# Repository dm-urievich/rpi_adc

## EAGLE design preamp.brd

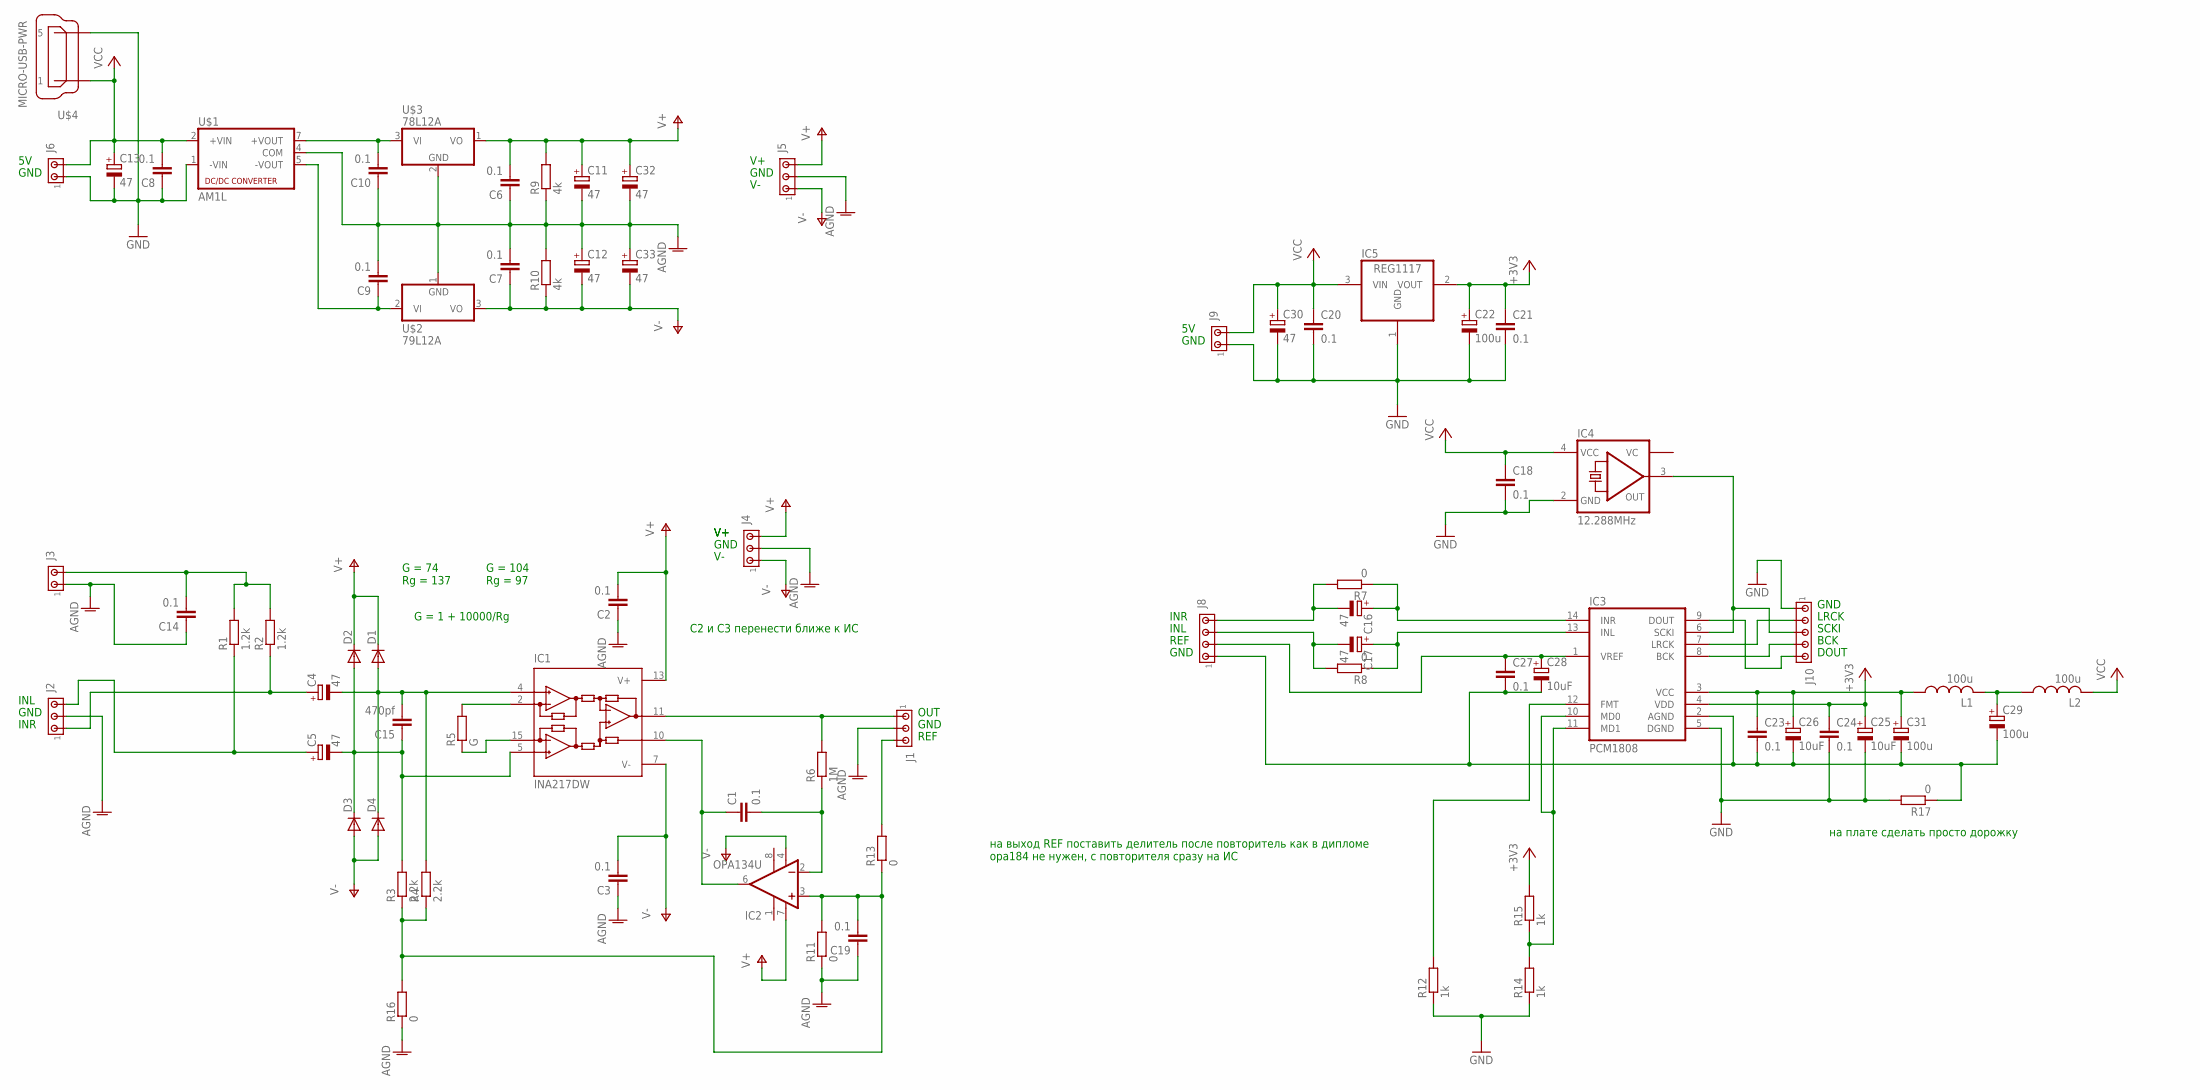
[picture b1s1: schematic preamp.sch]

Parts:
C1, C2, C3, C6, C7, C8, C9, C10, C14, C18, C19, C20, C21, C23, C24, C27: 0.1; C0805
C4, C5, C11, C12, C13, C16, C17, C30, C32, C33: 47; 153CLV-0605
C15: 470pf; C0805
C22, C29, C31: 100u; 153CLV-0605
C25, C26, C28: 10uF; SMC_A
D1, D2, D3, D4: DIODE-SOD123; SOD123
IC1: INA217DW; DW_RPDSO-G16
IC2: OPA134U; SO08
IC3: PCM1808; TSSOP14
IC4: 12.288MHz; KXO-97
IC5: REG1117; SOT223
J1, J2, J4, J5: MTA03-100; 10X03MTA
J3, J6, J9: MTA02-100; 10X02MTA
J8: MTA04-100; 10X04MTA
J10: MTA05-100; 10X05MTA
L1, L2: 100u; L3225M
R1, R2: 1.2k; R0805
R3, R4: 2.2k; R0805
R5: G; R0805
R6: 1M; R0805
R7, R8, R11, R13, R16, R17: 0; R0805
R9, R10: 4k; R0805
R12, R14, R15: 1k; R0805
U$1: AM1L; SO20
U$2: 79L12A; SOT89
U$3: 78L12A; SOT89
U$4: MICRO-USB-PWR; MICRO-USB

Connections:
+3V3: C21.1, C22.+, C24.1, C25.+, IC3.4 (VDD), IC5.2 (VOUT), R15.2
AGND: C2.1, C3.1, C6.1, C7.2, C9.2, C10.1, C11.-, C12.+, C14.1, C19.1, C32.-, C33.+, J1.2, J2.2, J3.1, J4.2, J5.2, R9.1, R10.2, R11.1, R16.1, U$1.4 (COM), U$2.1 (GND), U$3.2 (GND)
AGND2: C23.2, C26.-, C27.2, C28.-, C29.-, C31.-, IC3.2 (AGND), J8.1, R17.1
GND: C8.1, C13.-, C18.2, C20.2, C21.2, C22.-, C24.2, C25.-, C30.-, IC3.5 (DGND), IC4.2 (GND), IC5.1 (GND), J6.1, J9.1, J10.1, R12.1, R14.1, R17.2, U$1.1 (-VIN), U$4.5
unnamed: IC1.2 (RG1), R5.2
unnamed: IC1.15 (RG2), R5.1
unnamed: C5.-, C15.1, D2.A, D3.C, IC1.5 (+IN), R3.2
unnamed: C4.-, C15.2, D1.A, D4.C, IC1.4 (-IN), R4.2
unnamed: C4.+, J2.1, R2.1
unnamed: C5.+, J2.3, R1.1
unnamed: C10.2, U$1.7 (+VOUT), U$3.3 (VI)
unnamed: IC3.6 (SCKI), IC4.3 (OUT), J10.3
unnamed: IC3.9 (DOUT), J10.5
unnamed: C29.+, L1.2, L2.1
unnamed: C14.2, J3.2, R1.2, R2.2
unnamed: C1.2, IC2.2 (-IN), R6.1
unnamed: IC1.11 (OUT), J1.1, R6.2
unnamed: C1.1, IC1.10 (REF), IC2.6 (OUT)
unnamed: C9.1, U$1.5 (-VOUT), U$2.2 (VI)
unnamed: IC3.12 (FMT), R12.2
unnamed: IC3.7 (LRCK), J10.2
unnamed: IC3.8 (BCK), J10.4
unnamed: C27.1, C28.+, IC3.1 (VREF), J8.2
unnamed: C16.-, J8.4, R7.2
unnamed: C17.-, J8.3, R8.2
unnamed: C17.+, IC3.13 (INL), R8.1
unnamed: C16.+, IC3.14 (INR), R7.1
unnamed: IC3.10 (MD0), IC3.11 (MD1), R14.2, R15.1
unnamed: C23.1, C26.+, C31.+, IC3.3 (VCC), L1.1
unnamed: J1.3, R13.2
unnamed: C19.2, IC2.3 (+IN), R3.1, R4.1, R11.2, R13.1, R16.2
V+: C2.2, C6.2, C11.+, C32.+, D1.C, D2.C, IC1.13 (V+), IC2.7 (V+), J4.3, J5.3, R9.2, U$3.1 (VO)
V-: C3.2, C7.1, C12.-, C33.-, D3.A, D4.A, IC1.7 (V-), IC2.4 (V-), J4.1, J5.1, R10.1, U$2.3 (VO)
VCC: C8.2, C13.+, C18.1, C20.1, C30.+, IC4.4 (VCC), IC5.3 (VIN), J6.2, J9.2, L2.2, U$1.2 (+VIN), U$4.1

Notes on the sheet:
GND
INL
INR
OUT
REF
SCKI
LRCK
BCK
DOUT
на выход REF поставить делитель после повторитель как в дипломе opa184 не нужен, с повторителя сразу на ИС
С2 и С3 перенести ближе к ИС
G = 1 + 10000/Rg
G = 74 Rg = 137
G = 104 Rg = 97
на плате сделать просто дорожку

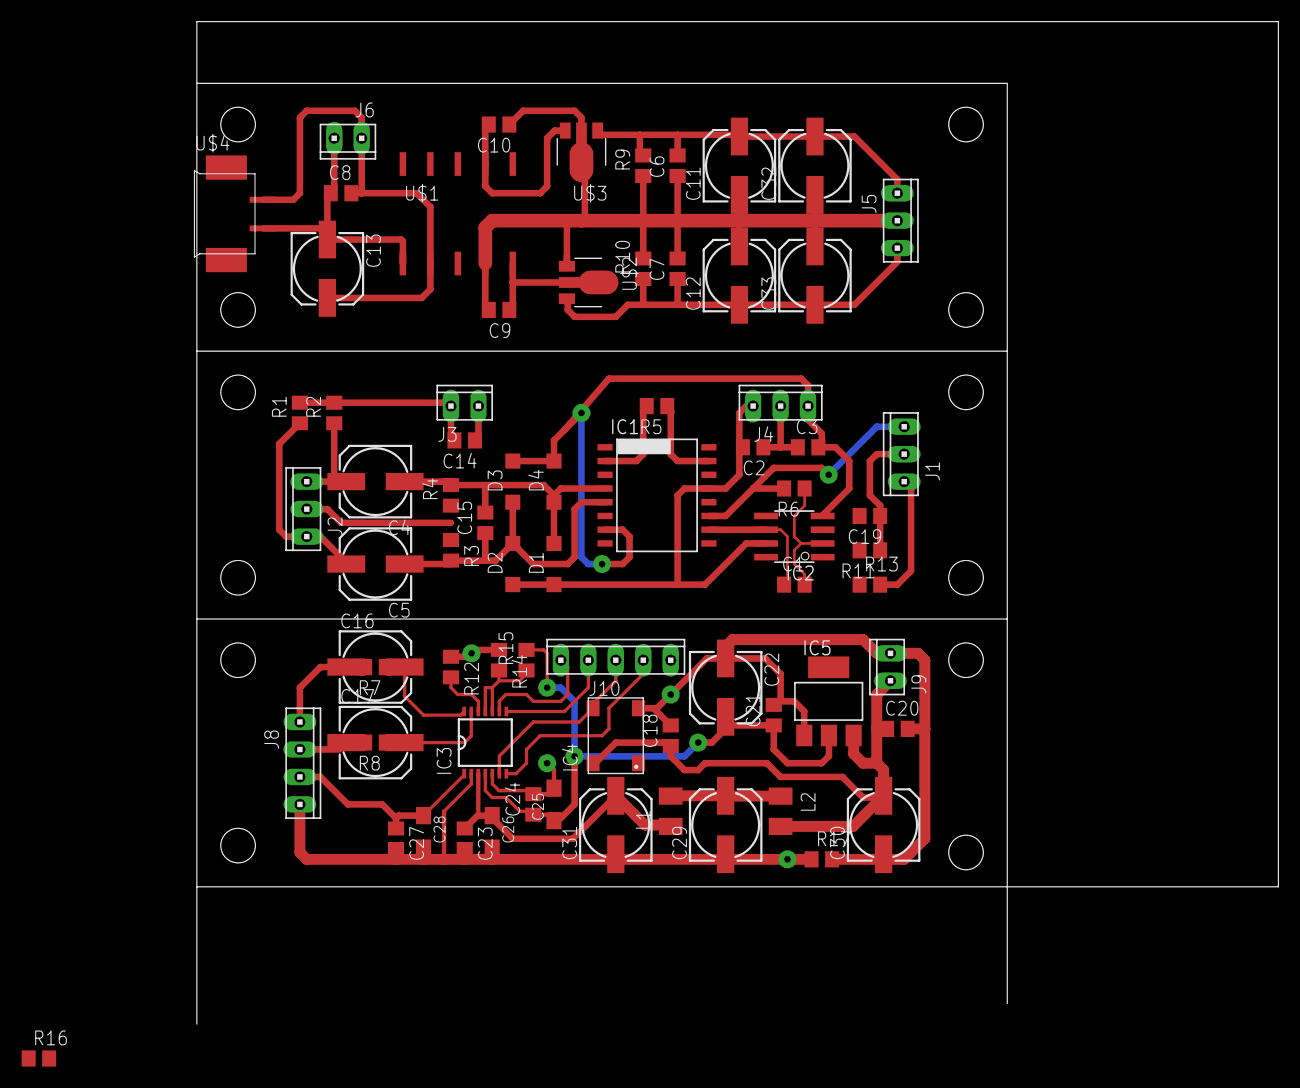
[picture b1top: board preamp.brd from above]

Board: 2 copper layers, 100.0 x 80.0 mm, 74 parts (0 on the bottom side), 34 nets.

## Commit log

2017-11-30 all schematic and ADC pcb
2017-11-30 after review: named wires, add divider to ref voltage, add GND to digital pins
2018-01-04 route preamp, check DRC 0.254 mm
2018-01-13 fix preamp dimentions, route power supply
2018-01-13 minor fixes in pcb
2018-01-16 move and rotate, copy preamp
2018-01-17 first production
2018-02-24 comment after soldering
